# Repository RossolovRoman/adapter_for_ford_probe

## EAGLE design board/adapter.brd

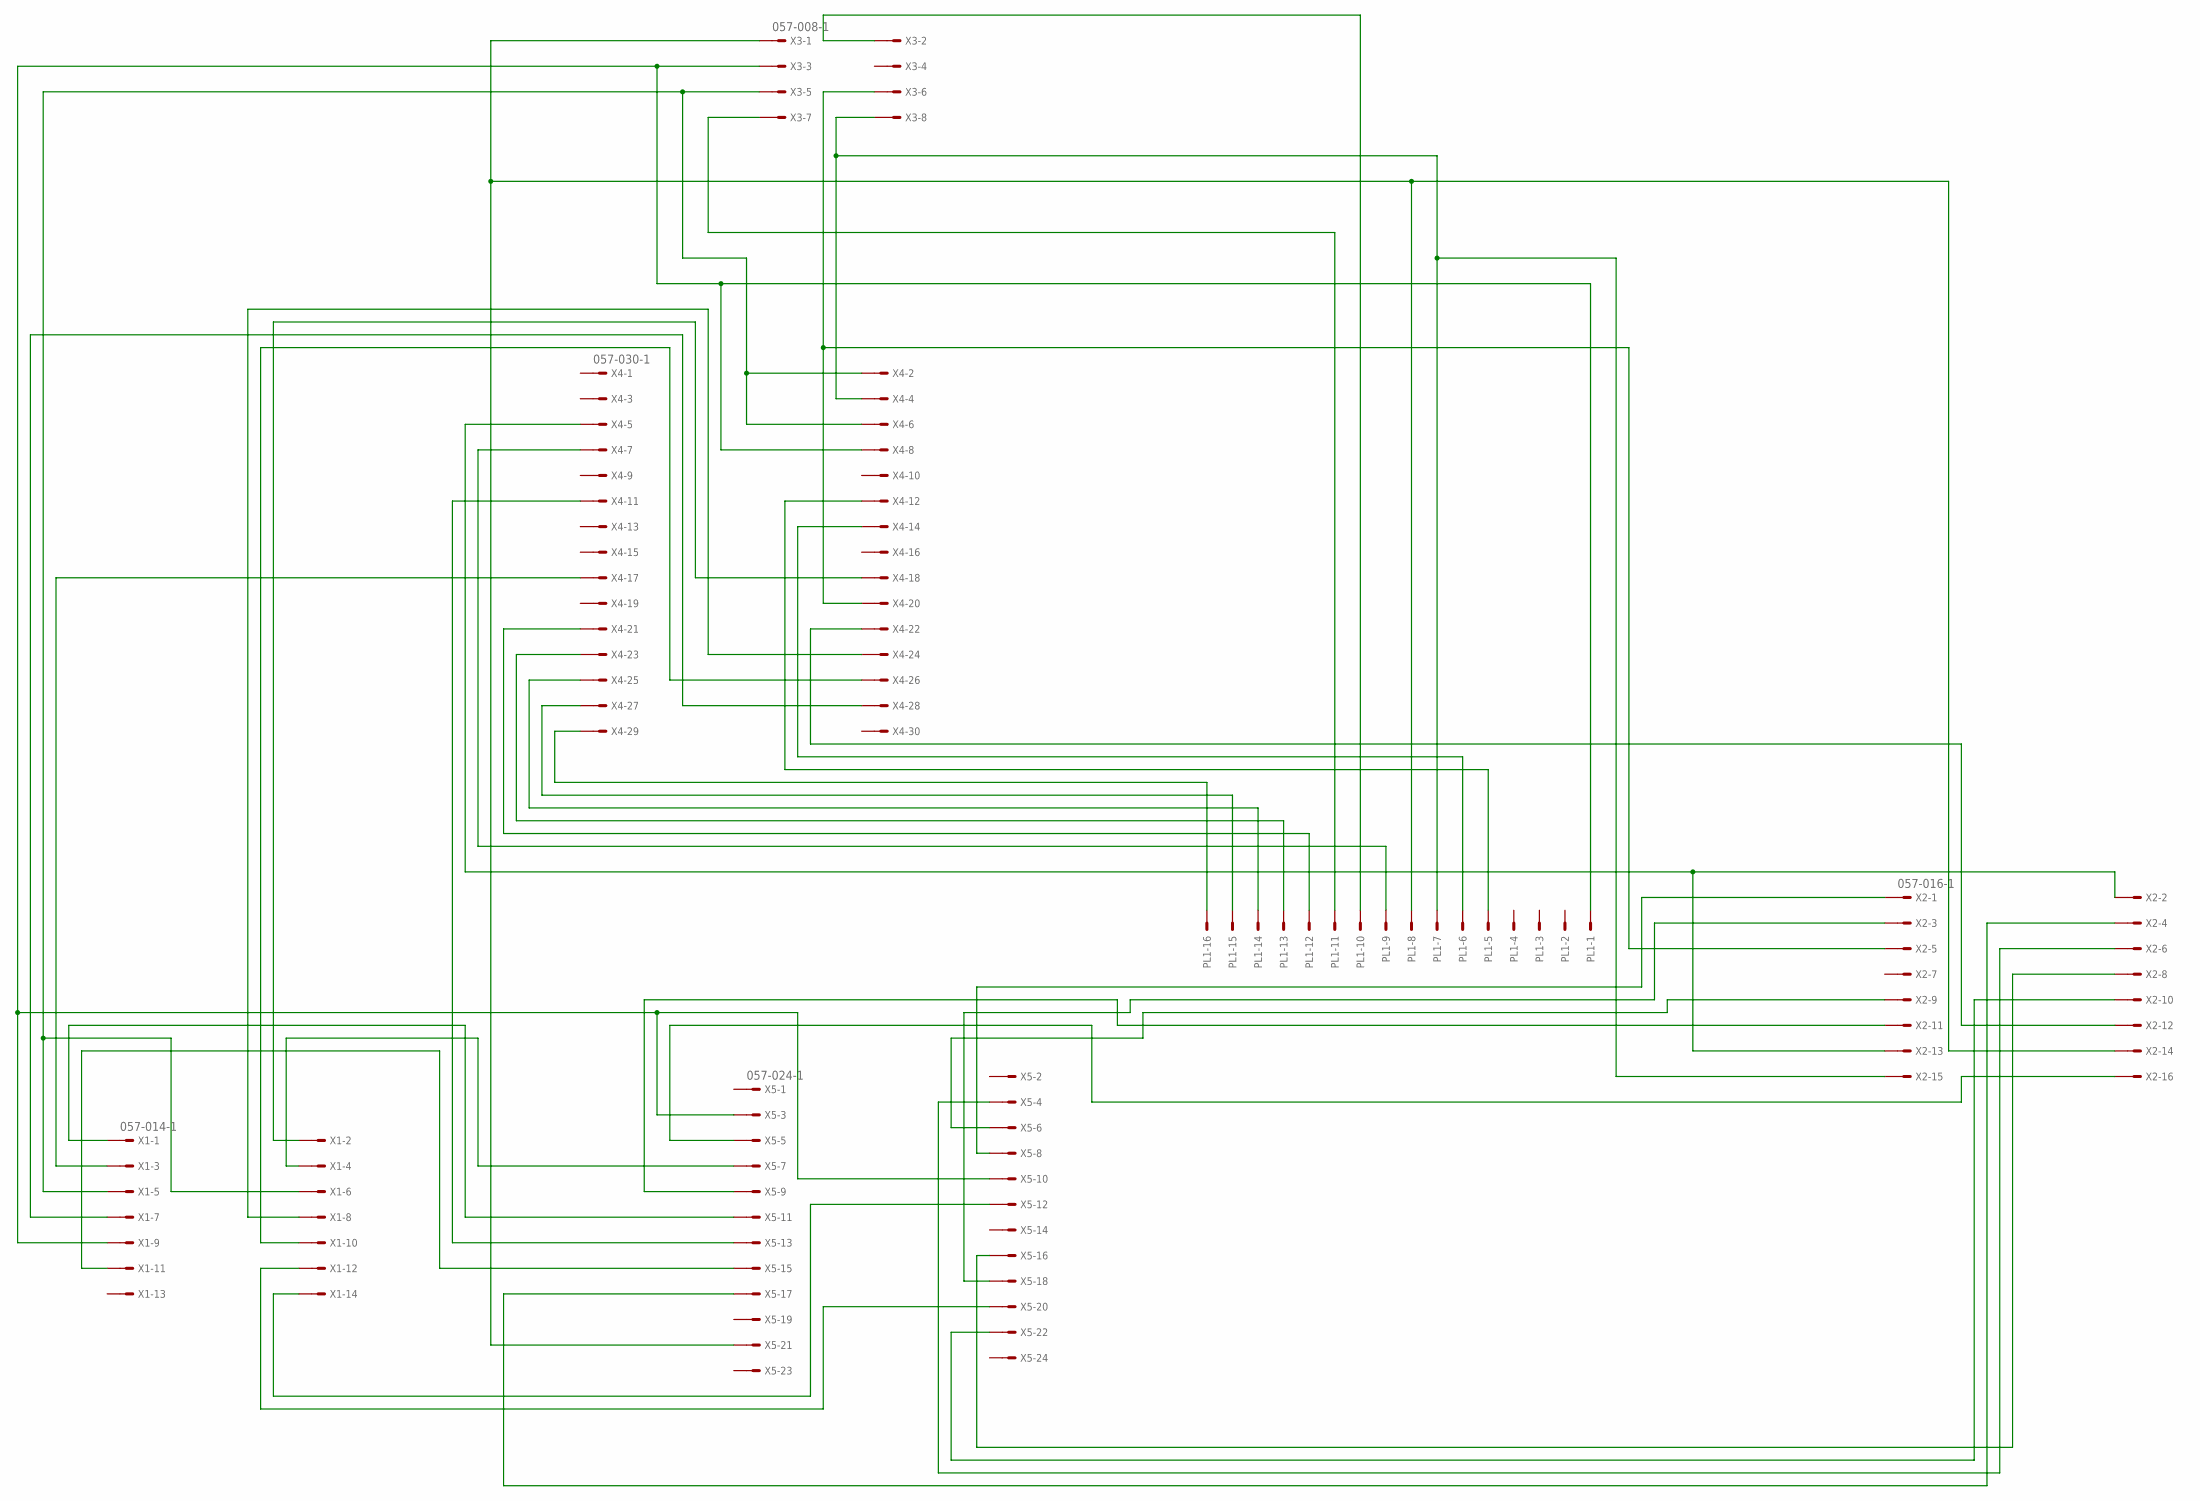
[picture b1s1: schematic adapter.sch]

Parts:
PL1: 555X-16V; 5566-16
X1: 057-014-1
X2: 057-016-1
X3: 057-008-1
X4: 057-030-1
X5: 057-024-1

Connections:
unnamed: PL1.11, X3.7
unnamed: X1.5, X1.6, X3.5, X4.2, X4.6
unnamed: PL1.8, X2.14, X3.1, X5.21
unnamed: PL1.7, X2.15, X3.8, X4.4
unnamed: PL1.1, X1.9, X3.3, X4.8, X5.3, X5.10
unnamed: X2.5, X3.6, X4.20
unnamed: PL1.10, X3.2
unnamed: PL1.6, X4.14
unnamed: PL1.5, X4.12
unnamed: PL1.16, X4.29
unnamed: PL1.15, X4.27
unnamed: PL1.14, X4.25
unnamed: PL1.13, X4.23
unnamed: PL1.12, X4.21
unnamed: PL1.9, X4.7
unnamed: X1.2, X4.18
unnamed: X1.7, X4.28
unnamed: X1.10, X4.26
unnamed: X1.8, X4.24
unnamed: X2.12, X4.22
unnamed: X2.2, X2.13, X4.5
unnamed: X4.11, X5.13
unnamed: X1.3, X4.17
unnamed: X1.1, X5.11
unnamed: X1.4, X5.7
unnamed: X1.11, X5.15
unnamed: X1.12, X5.20
unnamed: X1.14, X5.12
unnamed: X2.16, X5.5
unnamed: X2.11, X5.9
unnamed: X2.1, X5.8
unnamed: X2.3, X5.18
unnamed: X2.9, X5.6
unnamed: X2.4, X5.17
unnamed: X2.6, X5.4
unnamed: X2.10, X5.22
unnamed: X2.8, X5.16

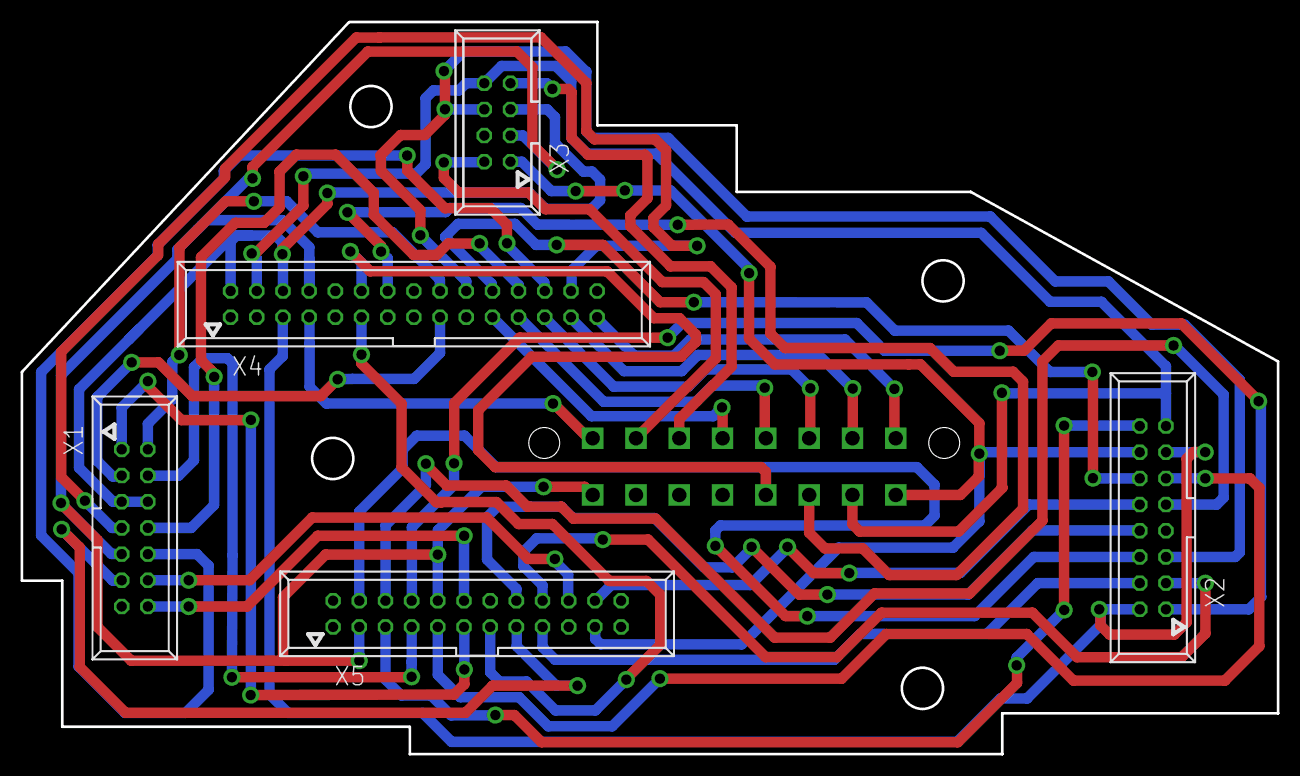
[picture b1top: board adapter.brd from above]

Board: 2 copper layers, 121.9 x 71.0 mm, 6 parts (1 on the bottom side), 37 nets.

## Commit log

2019-07-20 Добавлены эл. схема и плата устройства. Добавлены необходимые библиотеки.
